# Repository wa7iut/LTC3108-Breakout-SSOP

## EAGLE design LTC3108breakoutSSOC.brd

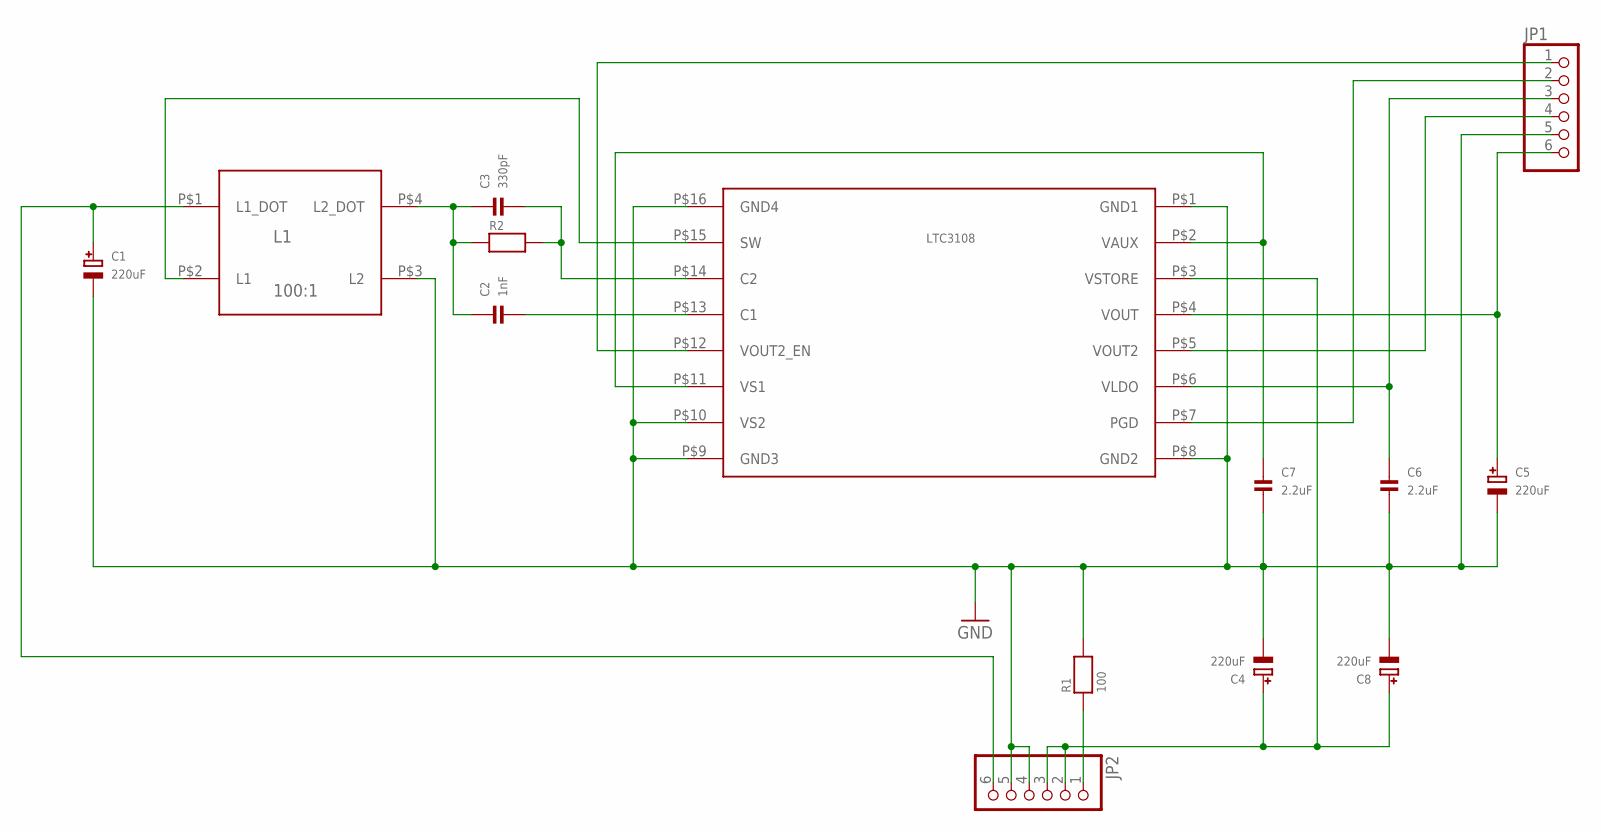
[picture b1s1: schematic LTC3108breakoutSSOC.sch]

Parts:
C1, C4, C5, C8: 220uF; EIA7343-31/D-R
C2: 1nF; 0603
C3: 330pF; 0603
C6, C7: 2.2uF; 0603
JP1, JP2: HEADER-1X6ROUND; 1X06_ROUND
L1: 100:1; COILCRAFT_LPR6235
LTC3108: LTC3108-SSOP; SSOP-GN-16
R1: 100; 0603
R2: RESISTOR0603; 0603

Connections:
GND: C1.-, C4.-, C5.-, C6.2, C7.2, C8.-, JP1.5, JP2.4, JP2.5, L1.P$3 (L2), LTC3108.P$1 (GND1), LTC3108.P$8 (GND2), LTC3108.P$9 (GND3), LTC3108.P$10 (VS2), LTC3108.P$16 (GND4), R1.2
unnamed: C1.+, JP2.6, L1.P$1 (L1_DOT)
unnamed: L1.P$2 (L1), LTC3108.P$15 (SW)
unnamed: C3.2, LTC3108.P$14 (C2), R2.2
unnamed: C2.2, LTC3108.P$13 (C1)
unnamed: C2.1, C3.1, L1.P$4 (L2_DOT), R2.1
unnamed: C7.1, LTC3108.P$2 (VAUX), LTC3108.P$11 (VS1)
unnamed: C4.+, C8.+, JP2.2, JP2.3, LTC3108.P$3 (VSTORE)
unnamed: C5.+, JP1.6, LTC3108.P$4 (VOUT)
unnamed: JP2.1, R1.1
unnamed: C6.1, JP1.3, LTC3108.P$6 (VLDO)
unnamed: JP1.1, LTC3108.P$12 (VOUT2_EN)
unnamed: JP1.2, LTC3108.P$7 (PGD)
unnamed: JP1.4, LTC3108.P$5 (VOUT2)

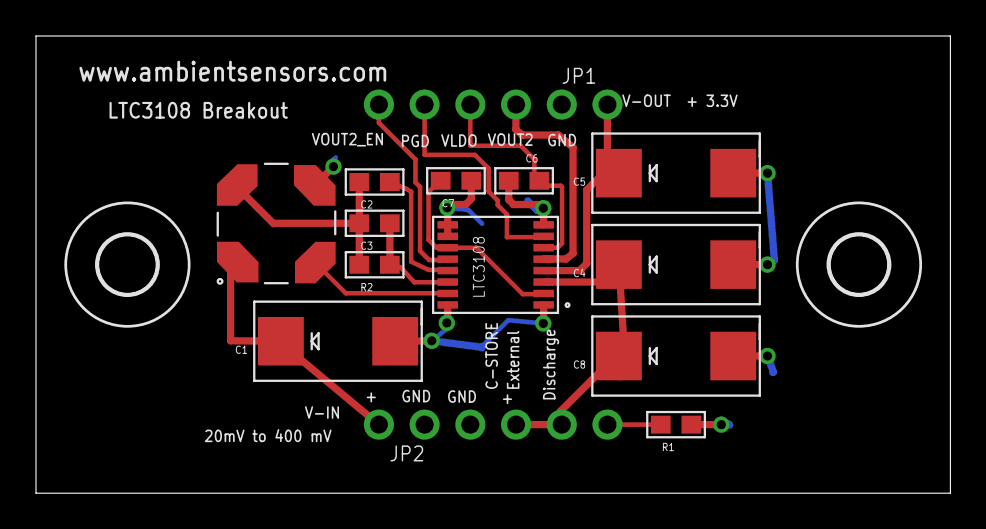
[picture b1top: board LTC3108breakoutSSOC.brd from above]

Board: 2 copper layers, 50.8 x 25.4 mm, 16 parts (0 on the bottom side), 14 nets.

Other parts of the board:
U$2, U$3: MOUNTINGHOLE_3.2

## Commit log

2011-07-17 initial project version
2011-07-18 file name changed
